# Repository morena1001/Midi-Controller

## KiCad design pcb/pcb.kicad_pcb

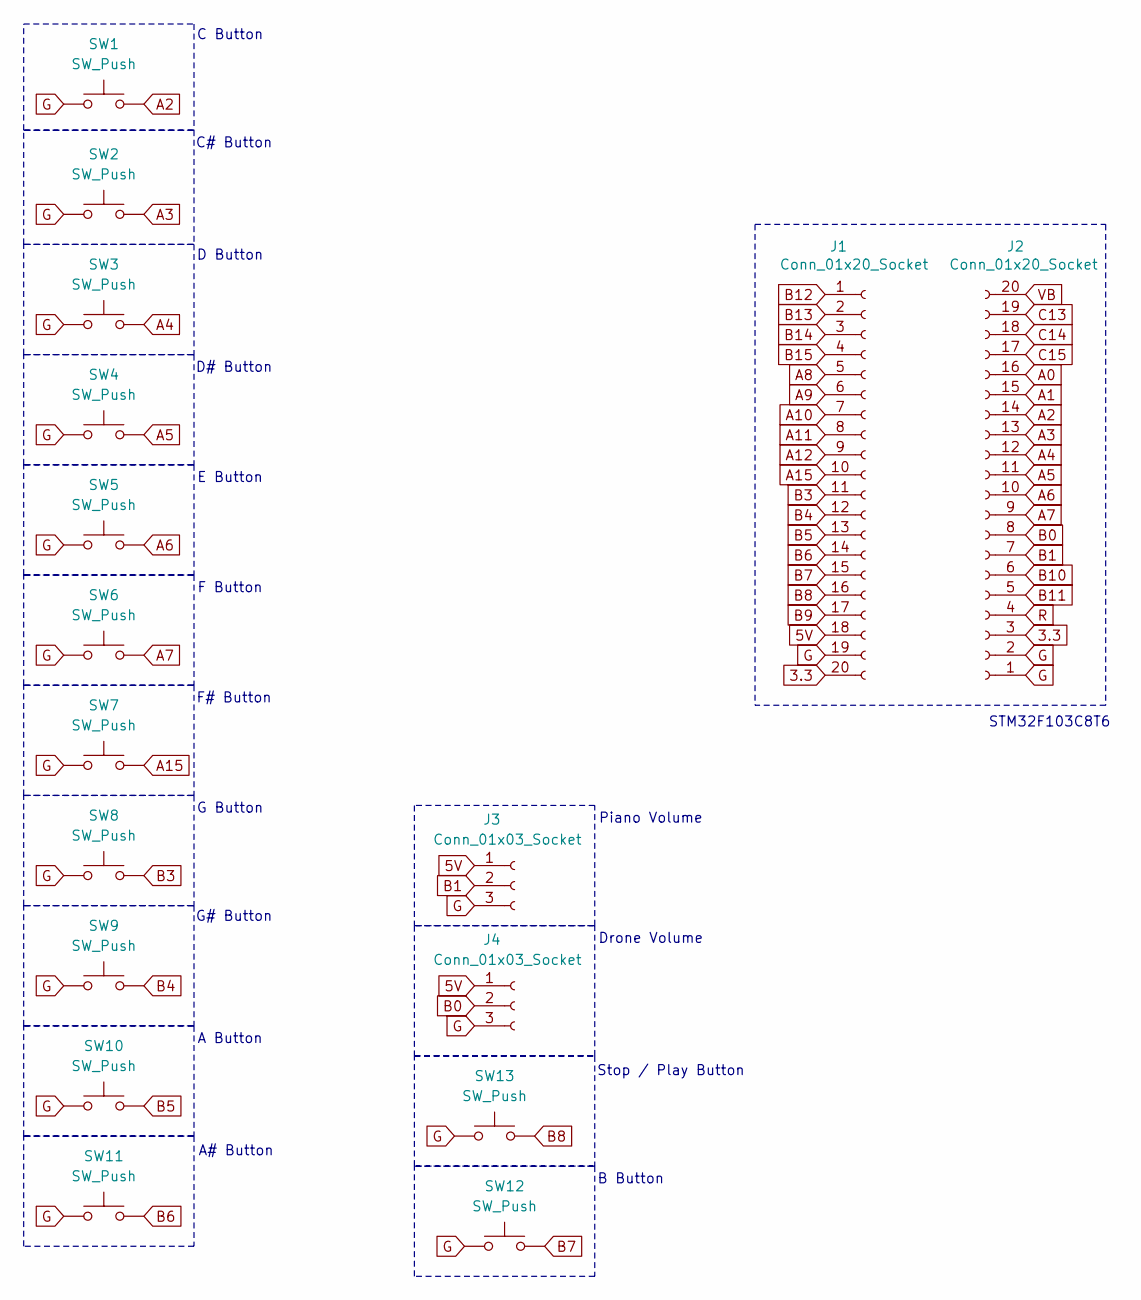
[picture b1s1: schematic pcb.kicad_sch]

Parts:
J1, J2: Conn_01x20_Socket; PinHeader_1x20_P2.54mm_Vertical
J3, J4: Conn_01x03_Socket; Potentiometer_Alpha_RD901F-40-00D_Single_Vertical_CircularH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
SW1, SW2, SW3, SW4, SW5, SW6, SW7, SW8, SW9, SW10, SW11, SW12, SW13: SW_Push; SW_Cherry_MX_1.00u_Plate

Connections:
3.3: J1.20, J2.3
5V: J1.18, J3.1, J4.1
A0: J2.16
A1: J2.15
A2: J2.14, SW1.2
A3: J2.13, SW2.2
A4: J2.12, SW3.2
A5: J2.11, SW4.2
A6: J2.10, SW5.2
A7: J2.9, SW6.2
A8: J1.5
A9: J1.6
A10: J1.7
A11: J1.8
A12: J1.9
A15: J1.10, SW7.2
B0: J2.8, J4.2
B1: J2.7, J3.2
B3: J1.11, SW8.2
B4: J1.12, SW9.2
B5: J1.13, SW10.2
B6: J1.14, SW11.2
B7: J1.15, SW12.2
B8: J1.16, SW13.2
B9: J1.17
B10: J2.6
B11: J2.5
B12: J1.1
B13: J1.2
B14: J1.3
B15: J1.4
C13: J2.19
C14: J2.18
C15: J2.17
G: J1.19, J2.1, J2.2, J3.3, J4.3, SW1.1, SW2.1, SW3.1, SW4.1, SW5.1, SW6.1, SW7.1, SW8.1, SW9.1, SW10.1, SW11.1, SW12.1, SW13.1
R: J2.4
VB: J2.20

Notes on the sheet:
G Button
B Button
Stop / Play Button
F Button
F# Button
C# Button
A# Button
C Button
Drone Volume
G# Button
D# Button
A Button
Piano Volume
D Button
STM32F103C8T6
E Button

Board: 2 copper layers, 17 parts (0 on the bottom side), 18 nets, no tracks yet.

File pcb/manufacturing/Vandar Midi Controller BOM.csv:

"Comment", "Designator", "Footprint"
"Conn_01x03_Socket", "J3,J4", "Potentiometer_THT:Potentiometer_Alpha_RD901F-40-00D_Single_Vertical_CircularHoles"
"SW_Push", "SW1,SW2,SW3,SW4,SW5,SW6,SW7,SW8,SW9,SW10,SW11,SW12,SW13", "Button_Switch_Keyboard:SW_Cherry_MX_1.00u_Plate"

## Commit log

2025-01-30 Can send out messages that are hopefully MIDI compliant or in correct MIDI format.
2025-01-30 still does not work
2025-02-21 CDC Communication works. Time to upgrade to Audio class
2025-06-02 Found a MIDI library on Github by Hypnotriod and Pieter12345, and proved very successful for my project. I was finally able to implement the basic MIDI controller that controlled the drone key and po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
2025-06-05 Added potentiometer feature, and connecting it to a slider on MainStage, let me control the volume. The only issue is the power supplies fluctuations. Aparently a capacitor connected from the ADC to 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
2025-06-08 Switched project over from the STM32F302R8 MCU to the STM32F103C8T6 MCU, also known as the blue pill. The final design use the blue pill for the reason that it is way more tiny than the first MCU. Ne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
2025-06-11 Created Folder to store documentation such as a task decomposition list and a folder to store progress reports
2025-06-11 Update Task Decomposition.md
    Task decomposition now shows current project progress
2025-06-13 Finished schematic for the pcb. Next is to create layout of pcb
2025-06-18 I accidentally set up the project using the wrong folder, so I hope this fixes it. All these new files are the real project. Anyway, fixed issues with ADC breaking the MIDI connection. Small crash wh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
2025-06-20 Finished PCB, needs hole testing to make sure components fit, and can then be sent to be manufactured
2025-06-29 Update task decomposition and added week 3 and 4 progress reports
2025-07-01 Added queue library to code. Next is to test that it works.
2025-07-02 Half finished. The queue works fine for the buttons, but there is an issue trying to enqueue the P_vol_message array. The D_vol_message works fine, which makes this all the more weirder.
2025-07-03 Finished feature. Code may or may not work without queue feature. Will need to test that.
2025-07-07 Added functionality for both potentiometers, with no more crashes.
2025-07-07 Added initial poll of potentiometers to match it to the software
2025-07-08 Finished issue 1: Inverse potentiometer value
2025-07-08 Finished issue 3: pre-timer polling not showing
